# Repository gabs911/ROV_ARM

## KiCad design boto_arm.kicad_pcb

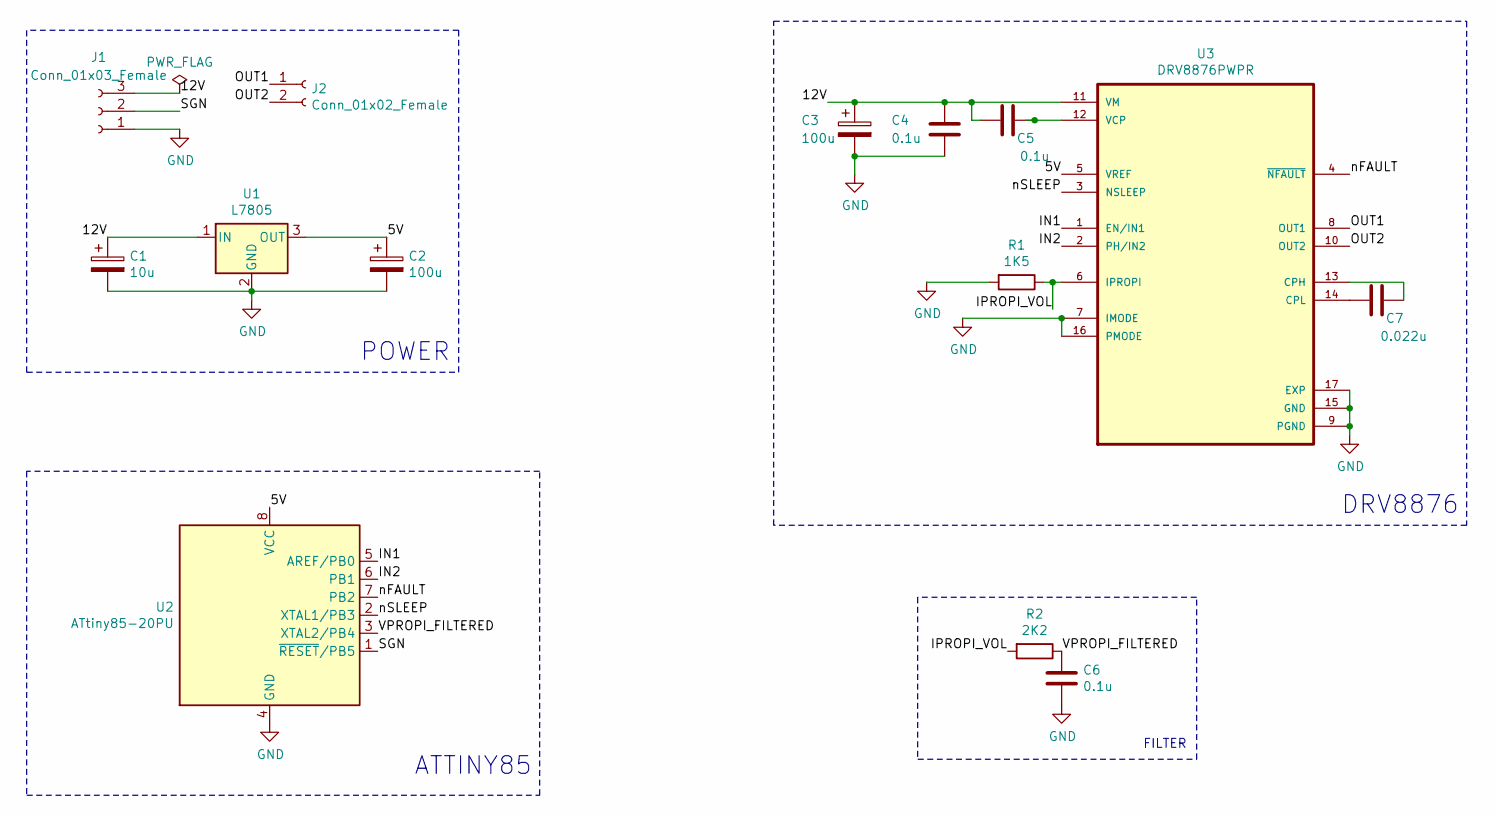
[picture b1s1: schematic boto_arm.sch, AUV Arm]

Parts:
C1: 10u; CP_Radial_D5.0mm_P2.00mm
C2, C3: 100u; CP_Radial_D5.0mm_P2.00mm
C4, C5, C6: 0.1u; C_Disc_D5.0mm_W2.5mm_P2.50mm
C7: 0.022u; C_Disc_D5.0mm_W2.5mm_P2.50mm
J1: Conn_01x03_Female; PinSocket_1x03_P2.54mm_Vertical
J2: Conn_01x02_Female; JST_EH_S2B-EH_1x02_P2.50mm_Horizontal
R1: 1K5; R_Axial_DIN0207_L6.3mm_D2.5mm_P7.62mm_Horizontal
R2: 2K2; R_Axial_DIN0207_L6.3mm_D2.5mm_P7.62mm_Horizontal
U1: L7805; TO-220-3_Vertical
U2: ATtiny85-20PU; DIP-8_W7.62mm
U3: DRV8876PWPR; IC_DRV8876PWPR; PARTREV E

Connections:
/5V: C2.1, U1.3 (OUT), U2.8 (VCC), U3.5 (VREF)
/12V: C1.1, C3.1, C4.2, C5.1, J1.3, U1.1 (IN), U3.11 (VM)
/IN1: U2.5 (AREF/PB0), U3.1 (EN/IN1)
/IN2: U2.6 (PB1), U3.2 (PH/IN2)
/IPROPI_VOL: R1.1, R2.2, U3.6 (IPROPI)
/OUT1: J2.1, U3.8 (OUT1)
/OUT2: J2.2, U3.10 (OUT2)
/SGN: J1.2, U2.1 (~RESET~/PB5)
/VPROPI_FILTERED: C6.1, R2.1, U2.3 (XTAL2/PB4)
/nFAULT: U2.7 (PB2), U3.4 (~NFAULT)
/nSLEEP: U2.2 (XTAL1/PB3), U3.3 (NSLEEP)
GND: C1.2, C2.2, C3.2, C4.1, C6.2, J1.1, R1.2, U1.2 (GND), U2.4 (GND), U3.7 (IMODE), U3.9 (PGND), U3.15 (GND), U3.16 (PMODE), U3.17 (EXP)
unnamed: C5.2, U3.12 (VCP)
unnamed: C7.1, U3.14 (CPL)
unnamed: C7.2, U3.13 (CPH)

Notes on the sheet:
DRV8876
FILTER
ATTINY85
POWER

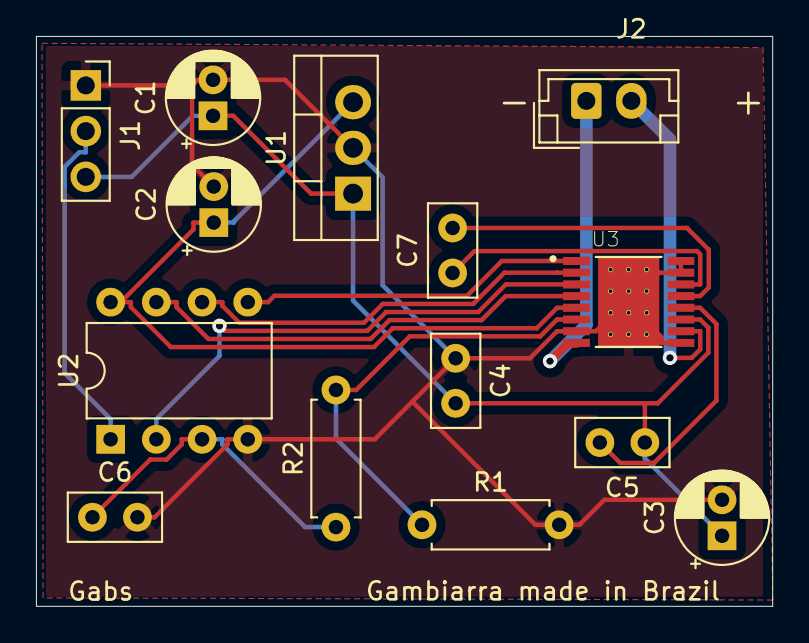
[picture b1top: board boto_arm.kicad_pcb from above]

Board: 2 copper layers, 40.9 x 31.7 mm, 14 parts (0 on the bottom side), 15 nets.

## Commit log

2021-03-21 Added schematic pdf
